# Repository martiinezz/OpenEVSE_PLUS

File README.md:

# OpenEVSE_PLUS+
README.md for OpenEVSE Hardware
Files SCH and BRD in KiCAD format
License CC BY-SA 3.0
OpenEVSE Hardware

Current Version OpenEVSE_PLUS_v4.

OpenEVSE_PLUS_v4 - Has 2 AC Detect chips like v1 + v2 plus the AC relay driver of v3. Added rectifier diodes to AC detect to improve detection in some conditions. Changed GFCI to individual pinout 4 pins.

Added 3,3V and 5V regulators. Board will be powered by cheap 12V power supplier instead of hard to get and expensive MPM AC/DC converter (at least in EEU). Will be also capable to have ESP8226 connected directly.

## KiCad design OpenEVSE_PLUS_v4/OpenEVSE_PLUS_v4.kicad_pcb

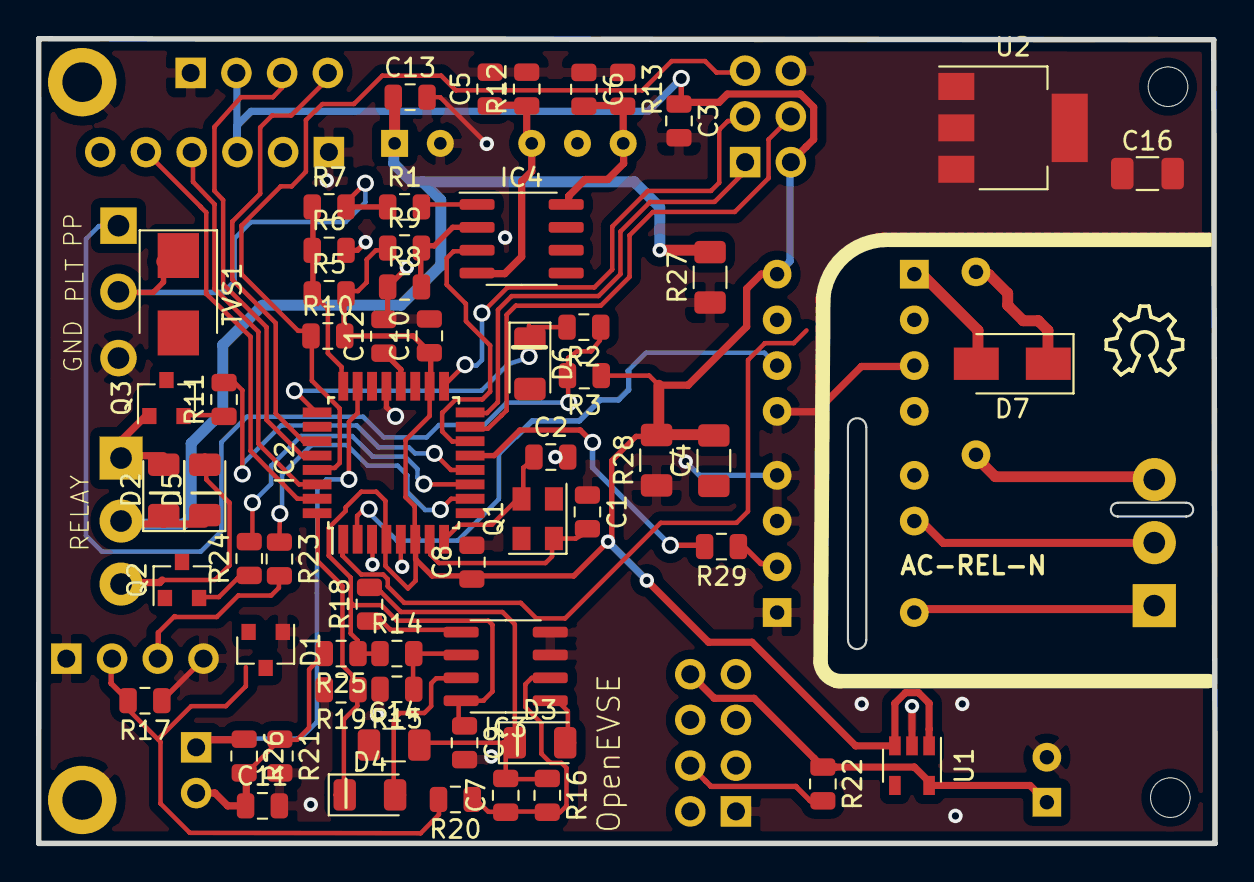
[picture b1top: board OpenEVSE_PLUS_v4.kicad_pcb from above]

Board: 2 copper layers, 65.4 x 44.7 mm, 78 parts (0 on the bottom side), 47 nets.

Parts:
.1: FTDI; PinHeader_1x06_P2.54mm_Vertical
A_CT1: M02PTH; PinHeader_1x02_P2.54mm_Vertical
C1, C2: 22pf; C_0805_2012Metric
C3, C7, C8, C9, C10, C11, C12: .1uf; C_0805_2012Metric
C4, C14: 10uf; C_1206_3216Metric
C5, C6: 1uf; C_0805_2012Metric
C13: 2.2uf; C_0805_2012Metric
C15: 100uF; CP_Radial_D5.0mm_P2.50mm
C16: 22uF; C_1206_3216Metric
D1: AZ23C5V6-7-F; SOT-23
D2, D3, D4, D5, D6: 1N4148; D_1206_3216Metric
D7: 1N4004; D_SMA
DCDC1: AIMTEC; Converter_DCDC_muRata_NMAxxxxSC_THT
G_CT1: G_CT; PinHeader_1x04_P2.54mm_Vertical
H1, H2: MountingHole_Pad; MountingHole_2.2mm_M2_DIN965_Pad
H3, H4: MountingHole; MountingHole_2.2mm_M2
I2C1: M04LOCK; PinHeader_1x04_P2.54mm_Vertical
IC1: MID400; DIP-8_W7.62mm
IC2: ATMEGA328P-AU; TQFP-32_7x7mm_P0.8mm
IC3: LM358; SOIC-8_3.9x4.9mm_P1.27mm
IC4: LF353; SOIC-8_3.9x4.9mm_P1.27mm
IC5: AQH1213; DIP-8-N7_W7.62mm
ISP1: AVRISP-6; PinHeader_2x03_P2.54mm_Vertical
J1: Conn_02x04_Odd_Even; PinSocket_2x04_P2.54mm_Vertical
LOGO1: OSHW_LOGO_8MILX0150-NT; OSHW_8X150_NOTEXT
PILOT1: Pilot; SCREWTERMINAL-3.5MM-3_LOCK.007S
Q1: 16000; Crystal_SMD_EuroQuartz_MT-4Pin_3.2x2.5mm
Q2, Q3: 2222A; SOT-23
R1: 620; R_0805_2012Metric
R2, R10, R19, R22: 10k; R_0805_2012Metric
R3, R20: 1k; R_0805_2012Metric
R4: 56k 1W; R_Axial_DIN0207_L6.3mm_D2.5mm_P10.16mm_Horizontal
R5: 56k; R_0805_2012Metric
R6, R8, R9, R14, R16, R21, R25: 100k; R_0805_2012Metric
R7: 200k; R_0805_2012Metric
R11, R17, R23, R24, R29: 330; R_0805_2012Metric
R12, R13: 2.4k; R_0805_2012Metric
R15: 20k; R_0805_2012Metric
R18: 100; R_0805_2012Metric
R26: 22; R_0805_2012Metric
R27: 330; R_1206_3216Metric
R28: 180; R_1206_3216Metric
RELAY1: M03SCREW_LOCK; TerminalBlock_Phoenix_PT-1,5-3-3.5-H_1x03_P3.50mm_Horizontal
RELAY2: AC; TerminalBlock_Phoenix_PT-1,5-3-3.5-H_1x03_P3.50mm_Horizontal
TVS1: P6SMB16CA; D_SMB
U1: SPX3819M5-L-3-3; SOT-23-5
U2: AMS1117-5.0; SOT-223-3_TabPin2

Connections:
+5V: .1.3, C3.1, C8.1, C9.1, C10.1, C16.1, I2C1.2, IC1.8, IC2.4, IC2.6, IC2.18, IC3.8, ISP1.2, R3.1, R5.2, R9.1, R10.2, R14.1, R25.1, R28.2, U1.1, U1.3, U2.2
+12V: C13.1, DCDC1.1, R27.2, RELAY1.2
/3-3v: C15.1, J1.8, R22.1, U1.5
/AC-N1: IC5.6, RELAY2.2
/AC-N2: IC5.8, RELAY2.1
/ACTST: R4.2, RELAY2.3
/AC_RELAY_1: IC2.13, R29.2
/AC_TEST_2: IC1.6, IC2.2
/AMP_READ: A_CT1.1, IC2.23, R26.1
/CH_PD: J1.4, R22.2
/DC_RELAY_1: IC2.11, R24.2
/DC_RELAY_2: IC2.12, R11.2
/GFCI_INT: IC2.32, R19.1
/GFCI_TEST: IC2.10, R23.1
/PILOT: PILOT1.2, R1.1, R7.2
/PILOTREAD: IC2.24, R5.1, R6.1, R7.1
/PP: PILOT1.1, R2.1, R3.2
/PP_READ: IC2.25, R2.2
/PWM: IC2.14, IC4.3
/RX-I: .1.4, IC2.30
/TX: .1.5, IC2.31
GND: .1.1, C1.1, C2.2, C3.2, C5.2, C6.1, C8.2, C9.2, C10.2, C11.2, C12.2, C13.2, C15.2, C16.2, D1.1, DCDC1.2, DCDC1.5, G_CT1.1, G_CT1.4, H1.1, H2.1, I2C1.1, IC1.3, IC1.5, IC2.3, IC2.5, IC2.21, IC3.3, IC3.4, IC5.1, IC5.3, IC5.4, ISP1.6, J1.1, PILOT1.3, Q1.1, Q1.3, Q2.2, Q3.2, R6.2, R8.1, R12.2, R13.1, R15.2, R17.1, R19.2, R21.2, R27.1, R28.1, U1.2, U2.1
unnamed: A_CT1.2, C11.1, R21.1, R25.2, R26.2
unnamed: C1.2, IC2.7, Q1.2
unnamed: C2.1, IC2.8, Q1.4
unnamed: C5.1, DCDC1.6, IC4.4, R12.1
unnamed: C6.2, DCDC1.4, IC4.8, R13.2
unnamed: C7.1, IC3.2, R16.2, R20.1
unnamed: C12.1, IC2.20
unnamed: C7.2, R16.1, R18.2
unnamed: D1.2, G_CT1.2, R17.2, R20.2
unnamed: Q3.3, RELAY1.1
unnamed: Q2.3, RELAY1.3
unnamed: G_CT1.3, R23.2
unnamed: I2C1.3, IC2.28
unnamed: I2C1.4, IC2.27
unnamed: IC2.15, ISP1.4
unnamed: IC2.16, ISP1.1
unnamed: IC2.17, ISP1.3
unnamed: IC2.29, ISP1.5, R10.1
unnamed: IC3.5, R18.1
unnamed: IC3.6, R14.2, R15.1
unnamed: IC4.1, R1.2
unnamed: IC4.2, R8.2, R9.2
unnamed: IC5.2, R29.1
unnamed: Q2.1, R24.1
unnamed: Q3.1, R11.1

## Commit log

2020-03-12 removed unwanted files and converted to KiCAD
2020-03-12 files cleanup
2020-03-13 removed non EU related parts
2020-03-13 removed some files again
2020-03-13 updated footprints to kicad
2020-03-14 added 3.3 and 5v regulators
